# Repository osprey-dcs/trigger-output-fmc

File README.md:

# Trigger Output FMC

A single width HPC FMC board which provides 16 low jitter TTL outputs,
along with two Si5394 jitter cleaners with outputs connected to the MGTREF capable
when matched with the [LBL Marble](https://github.com/BerkeleyLab/Marble) FMC carrier.

This design is Open Hardware created by Osprey DCS and published under the terms of the
[CERN Open Hardware Licence Version 2 - Strongly Reciprocal](cern_ohl_s_v2.txt) license.

This repository contains KiCad 9.0.4 design files.

- [Data sheet](datasheet.md)
- [Current generated](https://osprey-dcs.github.io/trigger-output-fmc/)
  - [Schematic](https://osprey-dcs.github.io/trigger-output-fmc/trigger-output-fmc-schematic.pdf)
  - [BoM](https://osprey-dcs.github.io/trigger-output-fmc/trigger-output-fmc-bom.csv)
  - [STeP model](https://osprey-dcs.github.io/trigger-output-fmc/3D/trigger-output-fmc-3D.step)
  - [QA Procedure](https://osprey-dcs.github.io/trigger-output-fmc/QA.html)

## Block Diagram

## Status

Revision 1.0 produced and tested.

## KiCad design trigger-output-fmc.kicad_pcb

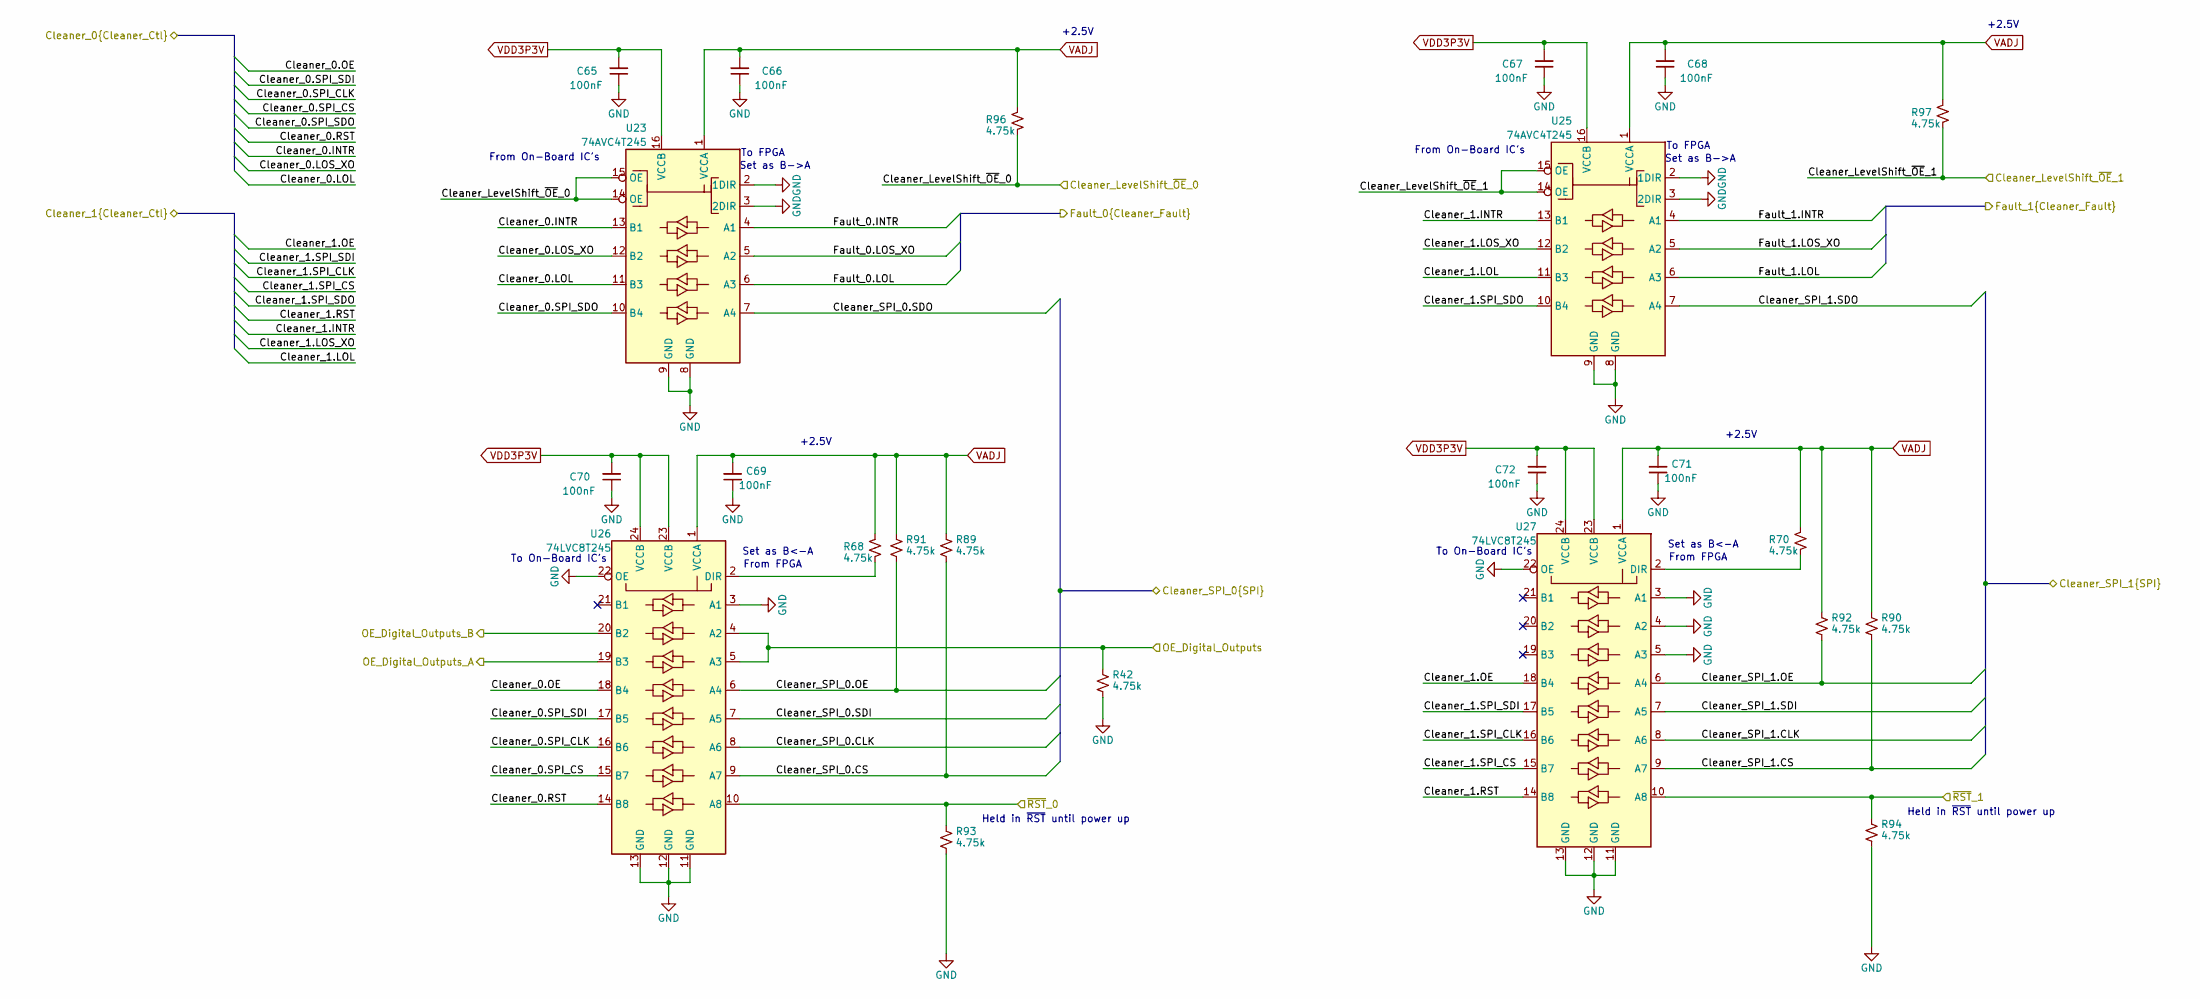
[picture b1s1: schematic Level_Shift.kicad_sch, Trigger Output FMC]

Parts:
C65, C66, C67, C68, C69, C70, C71, C72: 100nF; C_0402_1005Metric; MPN GCM155R71H104KE02J
R42, R68, R70, R89, R90, R91, R92, R93, R94, R96, R97: 4.75k; R_0402_1005Metric; MPN RC0402FR-074K75L
U23, U25: 74AVC4T245; TSSOP-16_4.4x5mm_P0.65mm; MPN SN74AVC4T245PWR
U26, U27: 74LVC8T245; TSSOP-24_4.4x7.8mm_P0.65mm; MPN SN74LVC8T245PWR

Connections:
/Digital IO/OE_A: U26.19 (B3); also elsewhere on the board
/Digital IO/OE_B: U26.20 (B2); also elsewhere on the board
/FMC/Cleaner_Fault_0.INTR: U23.4 (A1); also elsewhere on the board
/FMC/Cleaner_Fault_0.LOL: U23.6 (A3); also elsewhere on the board
/FMC/Cleaner_Fault_0.LOS_XO: U23.5 (A2); also elsewhere on the board
/FMC/Cleaner_Fault_1.INTR: U25.4 (A1); also elsewhere on the board
/FMC/Cleaner_Fault_1.LOL: U25.6 (A3); also elsewhere on the board
/FMC/Cleaner_Fault_1.LOS_XO: U25.5 (A2); also elsewhere on the board
/FMC/Cleaner_LevelShift_~OE_0: R96.1, U23.14 (OE), U23.15 (OE); also elsewhere on the board
/FMC/Cleaner_LevelShift_~OE_1: R97.1, U25.14 (OE), U25.15 (OE); also elsewhere on the board
/FMC/Cleaner_SPI_0.CLK: U26.8 (A6); also elsewhere on the board
/FMC/Cleaner_SPI_0.CS: R89.1, U26.9 (A7); also elsewhere on the board
/FMC/Cleaner_SPI_0.OE: R91.1, U26.6 (A4); also elsewhere on the board
/FMC/Cleaner_SPI_0.SDI: U26.7 (A5); also elsewhere on the board
/FMC/Cleaner_SPI_0.SDO: U23.7 (A4); also elsewhere on the board
/FMC/Cleaner_SPI_1.CLK: U27.8 (A6); also elsewhere on the board
/FMC/Cleaner_SPI_1.CS: R90.1, U27.9 (A7); also elsewhere on the board
/FMC/Cleaner_SPI_1.OE: R92.1, U27.6 (A4); also elsewhere on the board
/FMC/Cleaner_SPI_1.SDI: U27.7 (A5); also elsewhere on the board
/FMC/Cleaner_SPI_1.SDO: U25.7 (A4); also elsewhere on the board
/FMC/Cleaner_~RST_0: R93.2, U26.10 (A8); also elsewhere on the board
/FMC/Cleaner_~RST_1: R94.2, U27.10 (A8); also elsewhere on the board
/FMC/OE_Digital_Outputs: R42.2, U26.4 (A2), U26.5 (A3); also elsewhere on the board
/Jitter Cleaner0/Control.INTR: U23.13 (B1); also elsewhere on the board
/Jitter Cleaner0/Control.LOL: U23.11 (B3); also elsewhere on the board
/Jitter Cleaner0/Control.LOS_XO: U23.12 (B2); also elsewhere on the board
/Jitter Cleaner0/Control.OE: U26.18 (B4); also elsewhere on the board
/Jitter Cleaner0/Control.RST: U26.14 (B8); also elsewhere on the board
/Jitter Cleaner0/Control.SPI_CLK: U26.16 (B6); also elsewhere on the board
/Jitter Cleaner0/Control.SPI_CS: U26.15 (B7); also elsewhere on the board
/Jitter Cleaner0/Control.SPI_SDI: U26.17 (B5); also elsewhere on the board
/Jitter Cleaner0/Control.SPI_SDO: U23.10 (B4); also elsewhere on the board
/Jitter Cleaner1/Control.INTR: U25.13 (B1); also elsewhere on the board
/Jitter Cleaner1/Control.LOL: U25.11 (B3); also elsewhere on the board
/Jitter Cleaner1/Control.LOS_XO: U25.12 (B2); also elsewhere on the board
/Jitter Cleaner1/Control.OE: U27.18 (B4); also elsewhere on the board
/Jitter Cleaner1/Control.RST: U27.14 (B8); also elsewhere on the board
/Jitter Cleaner1/Control.SPI_CLK: U27.16 (B6); also elsewhere on the board
/Jitter Cleaner1/Control.SPI_CS: U27.15 (B7); also elsewhere on the board
/Jitter Cleaner1/Control.SPI_SDI: U27.17 (B5); also elsewhere on the board
/Jitter Cleaner1/Control.SPI_SDO: U25.10 (B4); also elsewhere on the board
GND: C65.1, C66.1, C67.1, C68.1, C69.1, C70.1, C71.1, C72.1, R42.1, R93.1, R94.1, U23.2 (1DIR), U23.3 (2DIR), U23.8 (GND), U23.9 (GND), U25.2 (1DIR), U25.3 (2DIR), U25.8 (GND), U25.9 (GND), U26.3 (A1), U26.11 (GND), U26.12 (GND), U26.13 (GND), U26.22 (OE), U27.3 (A1), U27.4 (A2), U27.5 (A3), U27.11 (GND), U27.12 (GND), U27.13 (GND), U27.22 (OE); also elsewhere on the board
unnamed: R68.1, U26.2 (DIR)
unnamed: R70.1, U27.2 (DIR)
VADJ: C66.2, C68.2, C69.2, C71.2, R68.2, R70.2, R89.2, R90.2, R91.2, R92.2, R96.2, R97.2, U23.1 (VCCA), U25.1 (VCCA), U26.1 (VCCA), U27.1 (VCCA); also elsewhere on the board
VDD3P3V: C65.2, C67.2, C70.2, C72.2, U23.16 (VCCB), U25.16 (VCCB), U26.23 (VCCB), U26.24 (VCCB), U27.23 (VCCB), U27.24 (VCCB); also elsewhere on the board

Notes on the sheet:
Held in ~{RST} until power up
To FPGA
To On-Board IC's
+2.5V
From On-Board IC's
Set as B<-A
From FPGA
Set as B->A
Set as B<-A

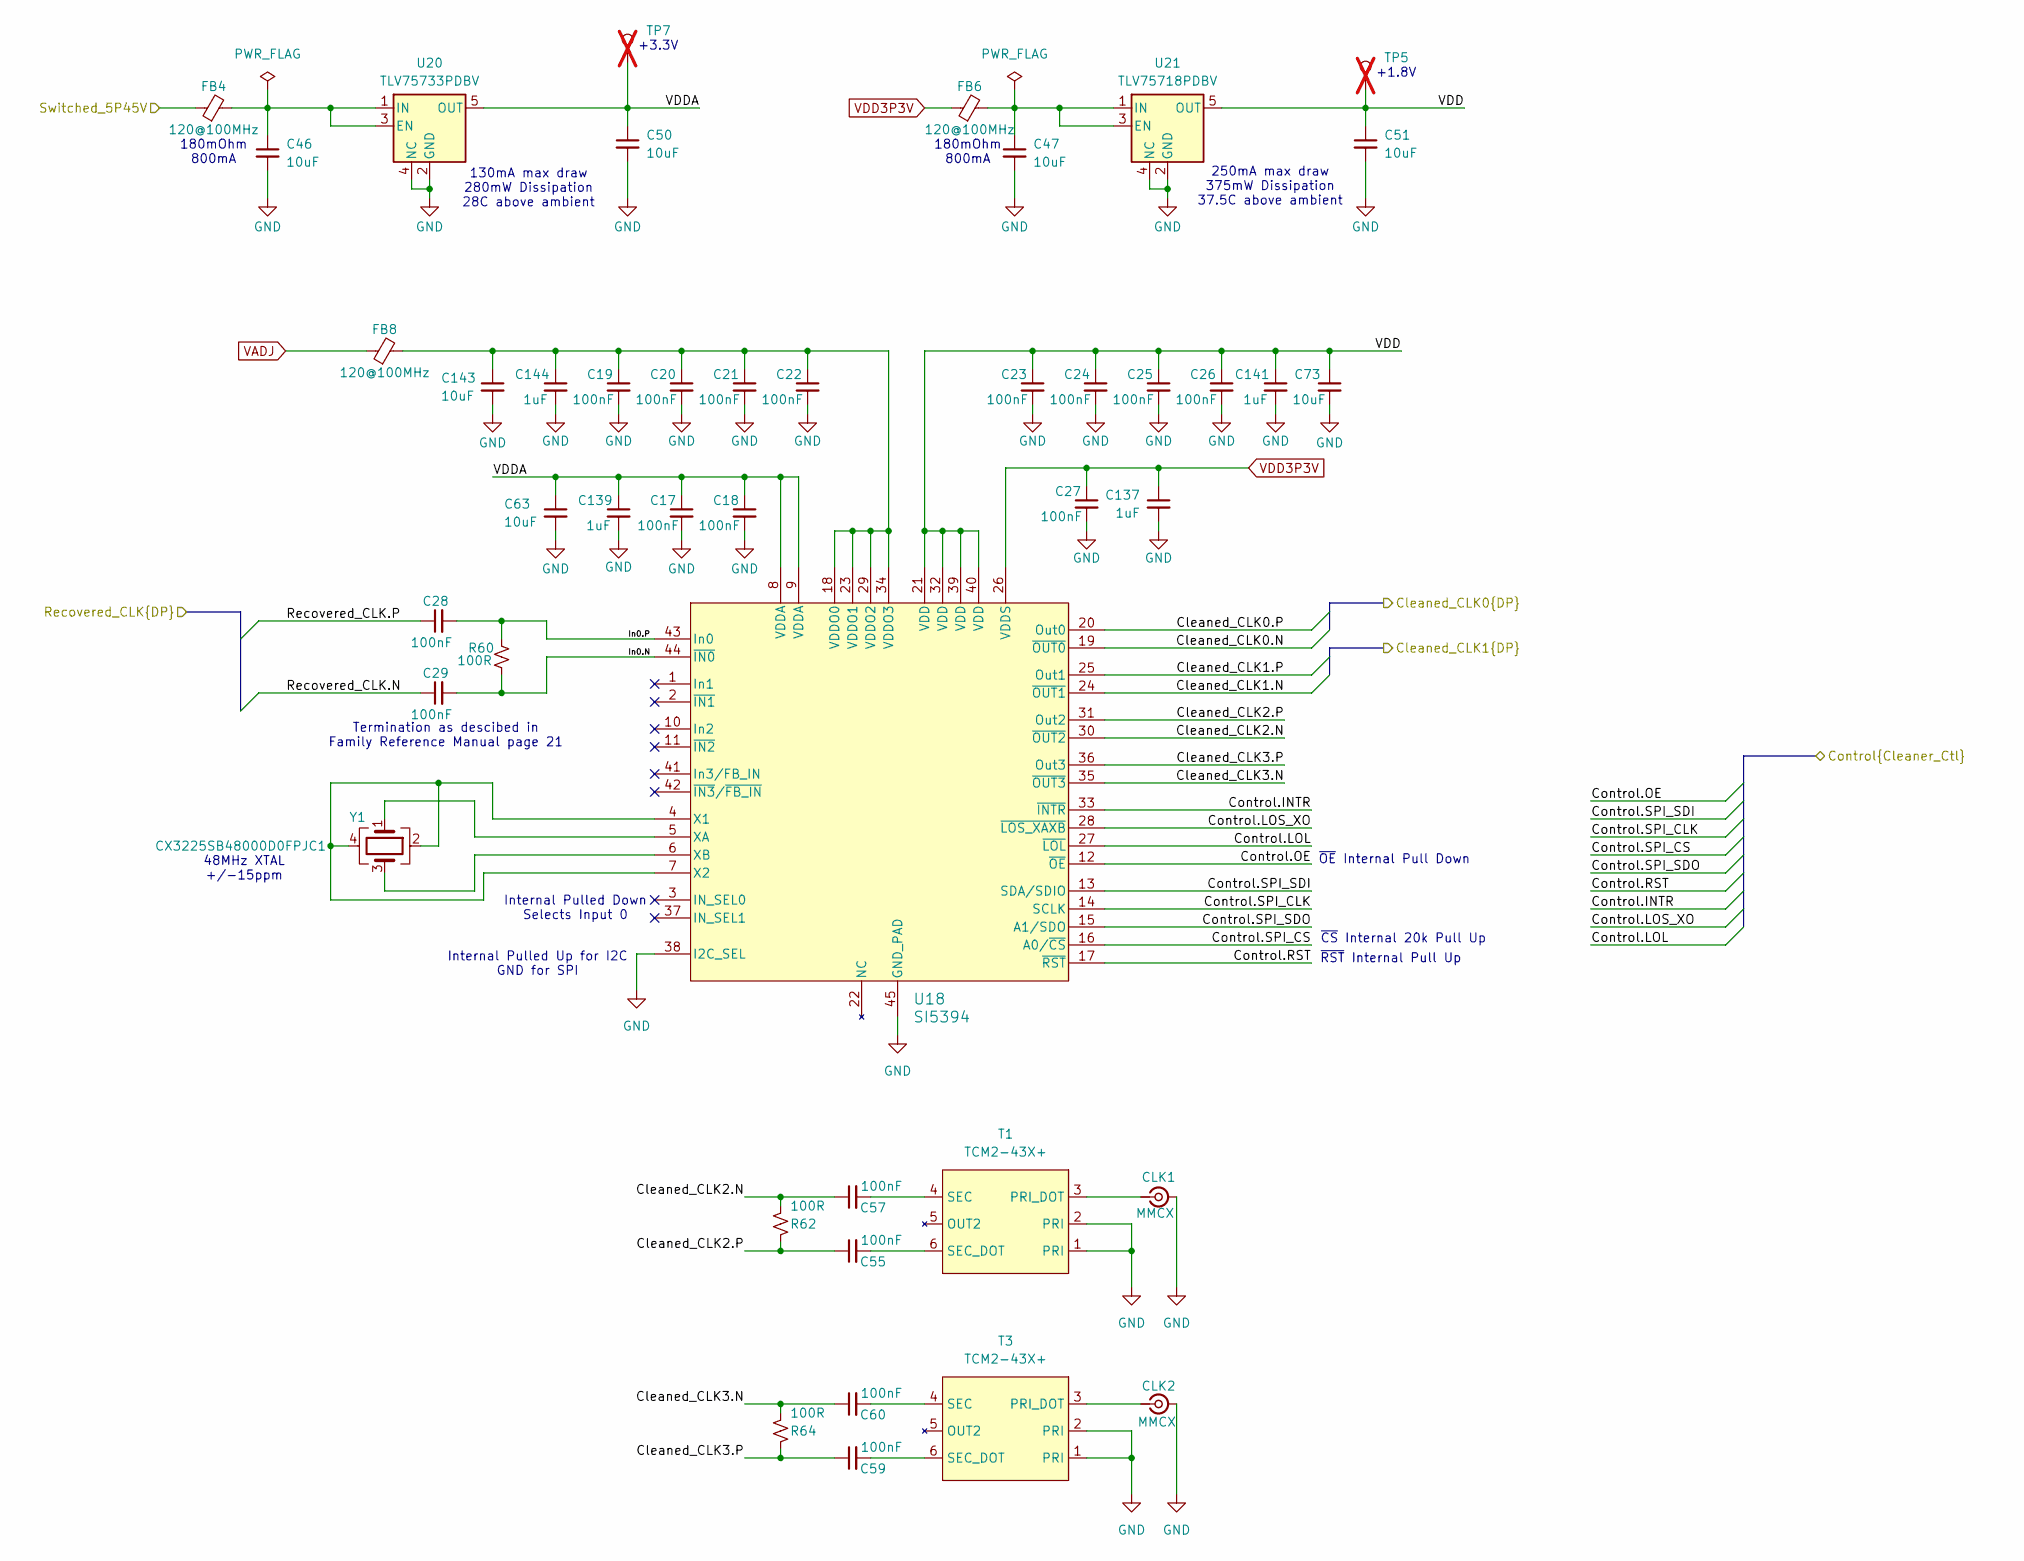
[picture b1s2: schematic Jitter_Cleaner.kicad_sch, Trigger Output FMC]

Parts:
C17, C18, C19, C20, C21, C22, C23, C24, C25, C26, C27, C28, C29, C55, C57, C59, C60: 100nF; C_0402_1005Metric; MPN GCM155R71H104KE02J
C46, C47, C50, C51, C63, C73, C143: 10uF; C_0805_2012Metric; MPN TMK212BBJ106MG-T
C137, C139, C141, C144: 1uF; C_0603_1608Metric; MPN GCM188R71E105KA64D
CLK1, CLK2: MMCX; MMCX_Molex_73415-1471_Vertical; MPN MMCX-J-P-H-ST-TH1
FB4, FB6, FB8: 120@100MHz; L_0603_1608Metric; MPN BLM18AG121SN1D
R60: 100R; R_0402_1005Metric; MPN RC0402FR-07100RL
R62, R64: 100R; R_0603_1608Metric; MPN RG1608P-101-B-T5
T1, T3: TCM2-43X+; Mini-Circuits_DB1627_rounded_pads; MPN TCM2-43X+
TP5, TP7: Keystone5000; TestPoint_Keystone_5000-5004_Miniature; MPN 5000; not fitted
U18: SI5394; QFN-44-1EP_7x7mm_P0.5mm_EP5.2x5.2mm_ThermalVias; MPN SI5394A-A-GM
U20: TLV75733PDBV; SOT-23-5; MPN TLV75733PDBV
U21: TLV75718PDBV; SOT-23-5; MPN TLV75718PDBV
Y1: CX3225SB48000D0FPJC1; Crystal_SMD_Abracon_ABM8AIG-4Pin_3.2x2.5mm; MPN CX3225SB48000D0FPJC1

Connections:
/Digital IO/Switched_5P45V: FB4.1; also elsewhere on the board
/FMC/Cleaned_CLK_0.N: U18.19 (~OUT0); also elsewhere on the board
/FMC/Cleaned_CLK_0.P: U18.20 (Out0); also elsewhere on the board
/FMC/FMC_GBTCLK0.N: U18.24 (~OUT1); also elsewhere on the board
/FMC/FMC_GBTCLK0.P: U18.25 (Out1); also elsewhere on the board
/FMC/Recovered_CLK_0.N: C29.1; also elsewhere on the board
/FMC/Recovered_CLK_0.P: C28.1; also elsewhere on the board
/Jitter Cleaner0/Cleaned_CLK2.N: C57.1, R62.2, U18.30 (~OUT2)
/Jitter Cleaner0/Cleaned_CLK2.P: C55.1, R62.1, U18.31 (Out2)
/Jitter Cleaner0/Cleaned_CLK3.N: C60.1, R64.2, U18.35 (~OUT3)
/Jitter Cleaner0/Cleaned_CLK3.P: C59.1, R64.1, U18.36 (Out3)
/Jitter Cleaner0/Control.INTR: U18.33 (~INTR); also elsewhere on the board
/Jitter Cleaner0/Control.LOL: U18.27 (~LOL); also elsewhere on the board
/Jitter Cleaner0/Control.LOS_XO: U18.28 (~LOS_XAXB); also elsewhere on the board
/Jitter Cleaner0/Control.OE: U18.12 (~OE); also elsewhere on the board
/Jitter Cleaner0/Control.RST: U18.17 (~RST); also elsewhere on the board
/Jitter Cleaner0/Control.SPI_CLK: U18.14 (SCLK); also elsewhere on the board
/Jitter Cleaner0/Control.SPI_CS: U18.16 (A0/~CS); also elsewhere on the board
/Jitter Cleaner0/Control.SPI_SDI: U18.13 (SDA/SDIO); also elsewhere on the board
/Jitter Cleaner0/Control.SPI_SDO: U18.15 (A1/SDO); also elsewhere on the board
/Jitter Cleaner0/In0.N: C29.2, R60.2, U18.44 (~IN0)
/Jitter Cleaner0/In0.P: C28.2, R60.1, U18.43 (In0)
/Jitter Cleaner0/VDD: C23.1, C24.1, C25.1, C26.1, C51.1, C73.1, C141.1, TP5.1, U18.21 (VDD), U18.32 (VDD), U18.39 (VDD), U18.40 (VDD), U21.5 (OUT)
/Jitter Cleaner0/VDDA: C17.1, C18.1, C50.1, C63.1, C139.1, TP7.1, U18.8 (VDDA), U18.9 (VDDA), U20.5 (OUT)
GND: C17.2, C18.2, C19.2, C20.2, C21.2, C22.2, C23.2, C24.2, C25.2, C26.2, C27.2, C46.2, C47.2, C50.2, C51.2, C63.2, C73.2, C137.2, C139.2, C141.2, C143.2, C144.2, CLK1.2 (Ext), CLK2.2 (Ext), T1.1 (PRI), T1.2 (PRI), T3.1 (PRI), T3.2 (PRI), U18.38 (I2C_SEL), U18.45 (GND_PAD), U20.2 (GND), U20.4 (NC), U21.2 (GND), U21.4 (NC); also elsewhere on the board
unnamed: CLK1.1 (In), T1.3 (PRI_DOT)
unnamed: CLK2.1 (In), T3.3 (PRI_DOT)
unnamed: C57.2, T1.4 (SEC)
unnamed: C55.2, T1.6 (SEC_DOT)
unnamed: C60.2, T3.4 (SEC)
unnamed: C59.2, T3.6 (SEC_DOT)
unnamed: C19.1, C20.1, C21.1, C22.1, C143.1, C144.1, FB8.2, U18.18 (VDDO0), U18.23 (VDDO1), U18.29 (VDDO2), U18.34 (VDDO3)
unnamed: U18.4 (X1), U18.7 (X2), Y1.2, Y1.4
unnamed: U18.5 (XA), Y1.1
unnamed: U18.6 (XB), Y1.3
unnamed: C46.1, FB4.2, U20.1 (IN), U20.3 (EN)
unnamed: C47.1, FB6.2, U21.1 (IN), U21.3 (EN)
VADJ: FB8.1; also elsewhere on the board
VDD3P3V: C27.1, C137.1, FB6.1, U18.26 (VDDS); also elsewhere on the board

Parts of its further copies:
C30, C31, C32, C36, C37, C38, C39, C40, C41, C42, C43, C44, C45, C56, C58, C61, C62: 100nF; C_0402_1005Metric; MPN GCM155R71H104KE02J
C64, C74, C75, C76, C77, C78, C145: 10uF; C_0805_2012Metric; MPN TMK212BBJ106MG-T
C138, C140, C142, C146: 1uF; C_0603_1608Metric; MPN GCM188R71E105KA64D
CLK3, CLK4: MMCX; MMCX_Molex_73415-1471_Vertical; MPN MMCX-J-P-H-ST-TH1
FB5, FB7, FB9: 120@100MHz; L_0603_1608Metric; MPN BLM18AG121SN1D
R61: 100R; R_0402_1005Metric; MPN RC0402FR-07100RL
R63, R65: 100R; R_0603_1608Metric; MPN RG1608P-101-B-T5
T2, T4: TCM2-43X+; Mini-Circuits_DB1627_rounded_pads; MPN TCM2-43X+
TP6, TP9: Keystone5000; TestPoint_Keystone_5000-5004_Miniature; MPN 5000; not fitted
U19: SI5394; QFN-44-1EP_7x7mm_P0.5mm_EP5.2x5.2mm_ThermalVias; MPN SI5394A-A-GM
U24: TLV75733PDBV; SOT-23-5; MPN TLV75733PDBV
U28: TLV75718PDBV; SOT-23-5; MPN TLV75718PDBV
Y2: CX3225SB48000D0FPJC1; Crystal_SMD_Abracon_ABM8AIG-4Pin_3.2x2.5mm; MPN CX3225SB48000D0FPJC1

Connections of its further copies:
/Digital IO/Switched_5P45V: FB5.1; also elsewhere on the board
/FMC/Cleaned_CLK_1.N: U19.24 (~OUT1); also elsewhere on the board
/FMC/Cleaned_CLK_1.P: U19.25 (Out1); also elsewhere on the board
/FMC/FMC_GBTCLK1.N: U19.19 (~OUT0); also elsewhere on the board
/FMC/FMC_GBTCLK1.P: U19.20 (Out0); also elsewhere on the board
/FMC/Recovered_CLK_1.N: C31.1; also elsewhere on the board
/FMC/Recovered_CLK_1.P: C30.1; also elsewhere on the board
/Jitter Cleaner1/Cleaned_CLK2.N: C58.1, R63.2, U19.30 (~OUT2)
/Jitter Cleaner1/Cleaned_CLK2.P: C56.1, R63.1, U19.31 (Out2)
/Jitter Cleaner1/Cleaned_CLK3.N: C62.1, R65.2, U19.35 (~OUT3)
/Jitter Cleaner1/Cleaned_CLK3.P: C61.1, R65.1, U19.36 (Out3)
/Jitter Cleaner1/Control.INTR: U19.33 (~INTR); also elsewhere on the board
/Jitter Cleaner1/Control.LOL: U19.27 (~LOL); also elsewhere on the board
/Jitter Cleaner1/Control.LOS_XO: U19.28 (~LOS_XAXB); also elsewhere on the board
/Jitter Cleaner1/Control.OE: U19.12 (~OE); also elsewhere on the board
/Jitter Cleaner1/Control.RST: U19.17 (~RST); also elsewhere on the board
/Jitter Cleaner1/Control.SPI_CLK: U19.14 (SCLK); also elsewhere on the board
/Jitter Cleaner1/Control.SPI_CS: U19.16 (A0/~CS); also elsewhere on the board
/Jitter Cleaner1/Control.SPI_SDI: U19.13 (SDA/SDIO); also elsewhere on the board
/Jitter Cleaner1/Control.SPI_SDO: U19.15 (A1/SDO); also elsewhere on the board
/Jitter Cleaner1/In0.N: C31.2, R61.2, U19.44 (~IN0)
/Jitter Cleaner1/In0.P: C30.2, R61.1, U19.43 (In0)
/Jitter Cleaner1/VDD: C41.1, C43.1, C44.1, C45.1, C74.1, C78.1, C142.1, TP9.1, U19.21 (VDD), U19.32 (VDD), U19.39 (VDD), U19.40 (VDD), U28.5 (OUT)
/Jitter Cleaner1/VDDA: C37.1, C39.1, C64.1, C76.1, C140.1, TP6.1, U19.8 (VDDA), U19.9 (VDDA), U24.5 (OUT)
GND: C32.2, C36.2, C37.2, C38.2, C39.2, C40.2, C41.2, C42.2, C43.2, C44.2, C45.2, C64.2, C74.2, C75.2, C76.2, C77.2, C78.2, C138.2, C140.2, C142.2, C145.2, C146.2, CLK3.2 (Ext), CLK4.2 (Ext), T2.1 (PRI), T2.2 (PRI), T4.1 (PRI), T4.2 (PRI), U19.38 (I2C_SEL), U19.45 (GND_PAD), U24.2 (GND), U24.4 (NC), U28.2 (GND), U28.4 (NC); also elsewhere on the board
unnamed: CLK3.1 (In), T2.3 (PRI_DOT)
unnamed: CLK4.1 (In), T4.3 (PRI_DOT)
unnamed: C58.2, T2.4 (SEC)
unnamed: C56.2, T2.6 (SEC_DOT)
unnamed: C62.2, T4.4 (SEC)
unnamed: C61.2, T4.6 (SEC_DOT)
unnamed: C32.1, C36.1, C38.1, C40.1, C145.1, C146.1, FB9.2, U19.18 (VDDO0), U19.23 (VDDO1), U19.29 (VDDO2), U19.34 (VDDO3)
unnamed: U19.4 (X1), U19.7 (X2), Y2.2, Y2.4
unnamed: U19.5 (XA), Y2.1
unnamed: U19.6 (XB), Y2.3
unnamed: C75.1, FB5.2, U24.1 (IN), U24.3 (EN)
unnamed: C77.1, FB7.2, U28.1 (IN), U28.3 (EN)
VADJ: FB9.1; also elsewhere on the board
VDD3P3V: C42.1, C138.1, FB7.1, U19.26 (VDDS); also elsewhere on the board

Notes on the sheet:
130mA max draw 280mW Dissipation 28C above ambient
~{CS} Internal 20k Pull Up
Internal Pulled Up for I2C GND for SPI
48MHz XTAL +/-15ppm
180mOhm 800mA
250mA max draw 375mW Dissipation 37.5C above ambient
~{RST} Internal Pull Up
Termination as descibed in Family Reference Manual page 21
+1.8V
+3.3V
Internal Pulled Down Selects Input 0
~{OE} Internal Pull Down

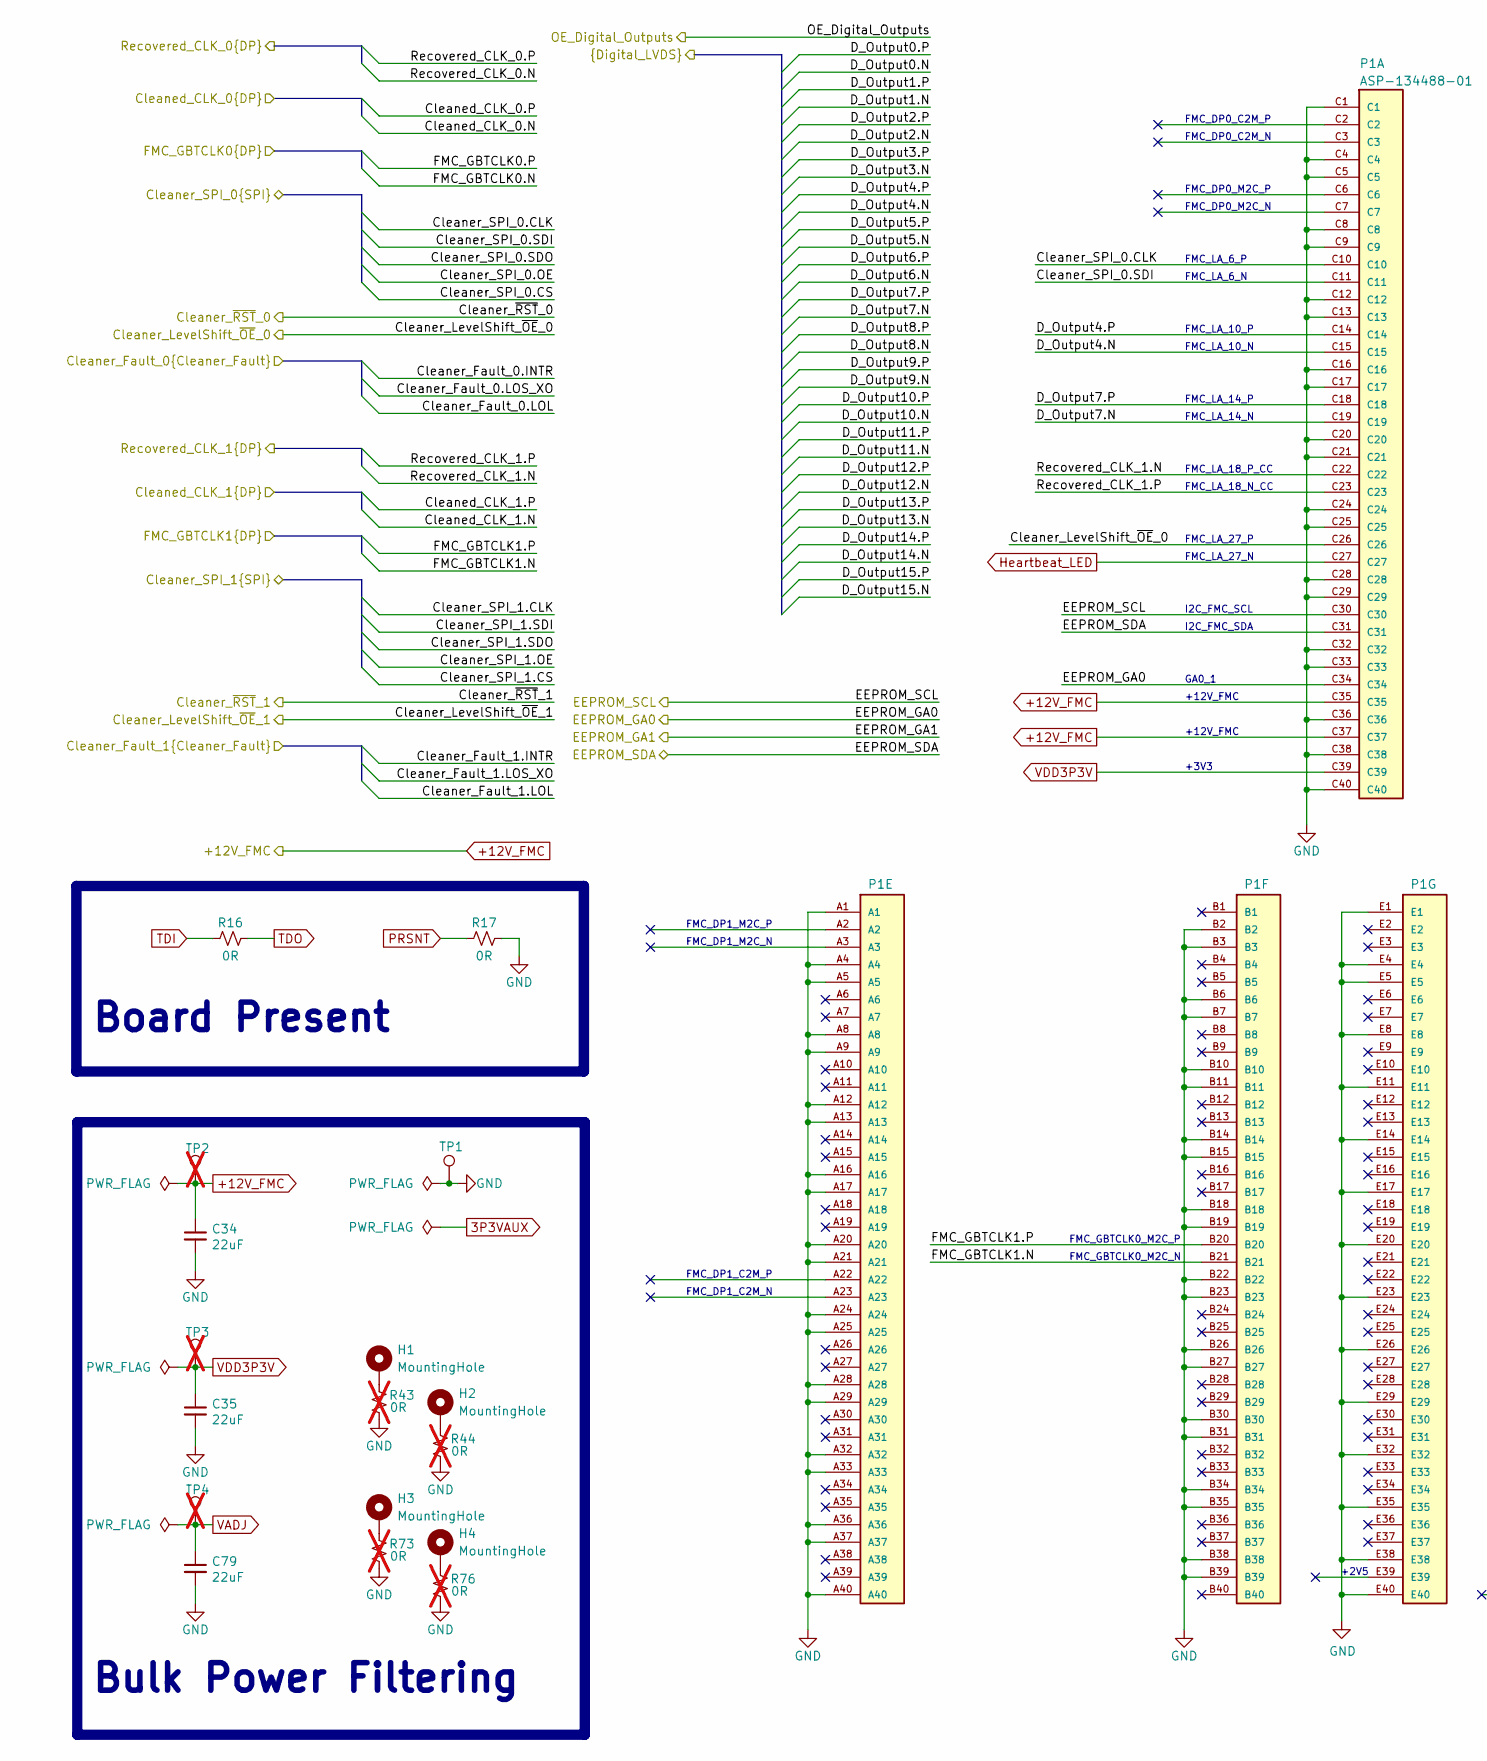
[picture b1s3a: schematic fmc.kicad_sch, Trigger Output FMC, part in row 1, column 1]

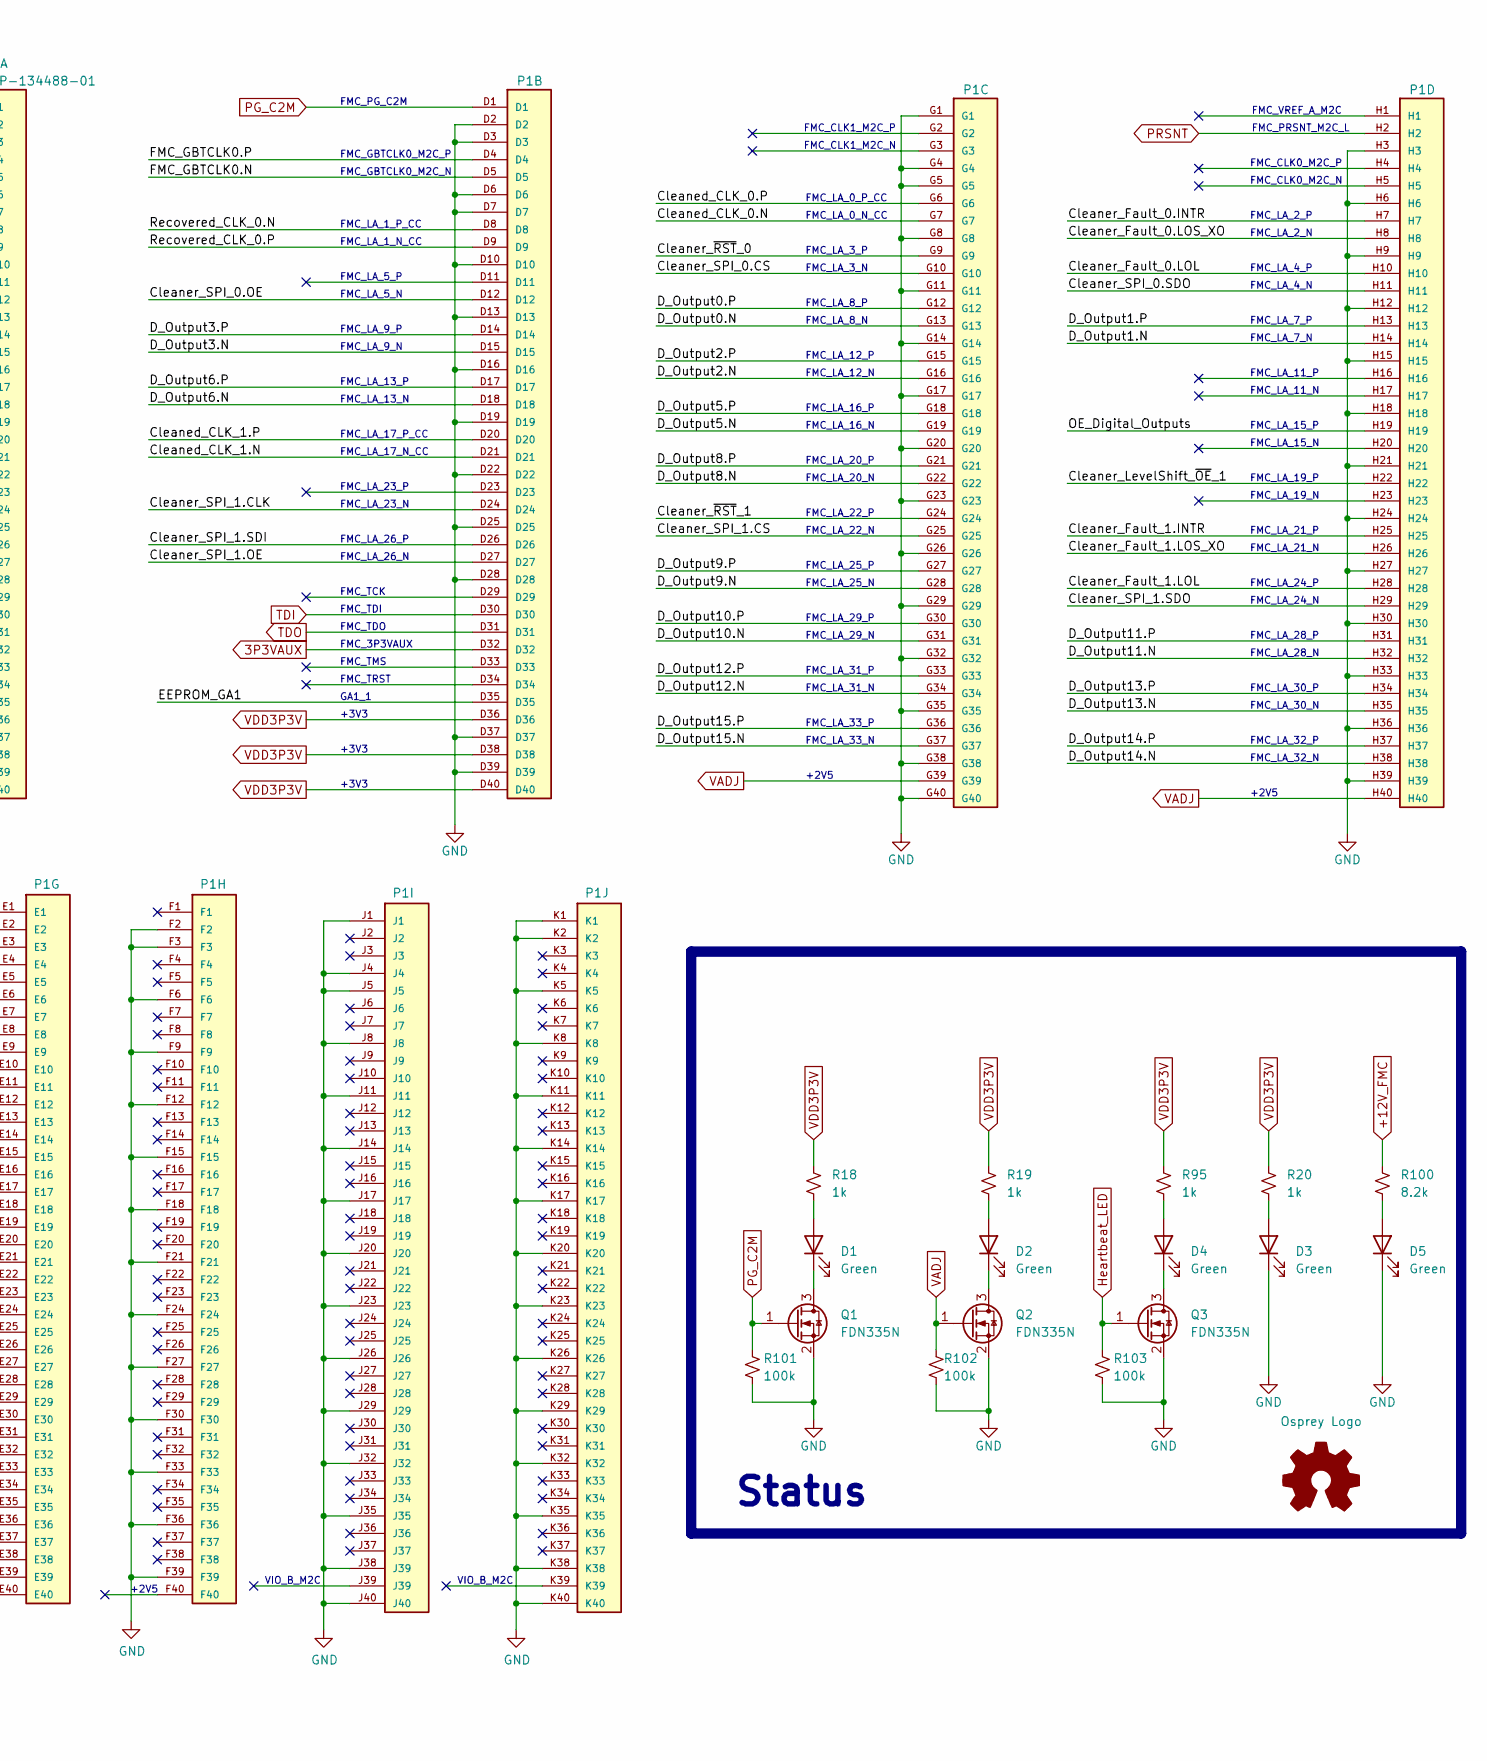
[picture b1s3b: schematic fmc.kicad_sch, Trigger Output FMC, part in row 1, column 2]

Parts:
C34, C35, C79: 22uF; C_1210_3225Metric; MPN GMK325BJ226MM-P
D1, D2, D3, D4, D5: Green; LED_0603_1608Metric; MPN APT1608CGCK
H1, H2: MountingHole; MountingHole_3.0mm_M2.5_Pad_3.3mm_UniversalMarbleSlot
H3, H4: MountingHole; MountingHole_3.0mm_3.8mm_Pad_3.3mm_UniversalMarbleSlot
Logo1: Osprey Logo; Logo_2X
P1: ASP-134488-01; Samtec_FMC_ASP-134602-01_10x40_P1.27mm_Vertical; MPN ASP-134488-01
Q1, Q2, Q3: FDN335N; SOT-23; MPN FDN335N
R16, R17: 0R; R_0603_1608Metric; MPN ERJ-3GEY0R00V
R18, R19, R20, R95: 1k; R_0603_1608Metric; MPN ESR03EZPF1001
R43, R44, R73, R76: 0R; R_0805_2012Metric; not fitted
R100: 8.2k; R_0603_1608Metric; MPN RC0603FR-078K2L
R101, R102, R103: 100k; R_0603_1608Metric; MPN RC0603FR-07100KL
TP1: Keystone5001; TestPoint_Keystone_5000-5004_Miniature; MPN 5001
TP2, TP3, TP4: Keystone5000; TestPoint_Keystone_5000-5004_Miniature; MPN 5000; not fitted

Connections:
3P3VAUX: P1.D32; also elsewhere on the board
+12V_FMC: C34.1, P1.C35, P1.C37, R100.2, TP2.1; also elsewhere on the board
/Digital IO/D_Output0.N: P1.G13; also elsewhere on the board
/Digital IO/D_Output0.P: P1.G12; also elsewhere on the board
/Digital IO/D_Output1.N: P1.H14; also elsewhere on the board
/Digital IO/D_Output1.P: P1.H13; also elsewhere on the board
/Digital IO/D_Output2.N: P1.G16; also elsewhere on the board
/Digital IO/D_Output2.P: P1.G15; also elsewhere on the board
/Digital IO/D_Output3.N: P1.D15; also elsewhere on the board
/Digital IO/D_Output3.P: P1.D14; also elsewhere on the board
/Digital IO/D_Output4.N: P1.C15; also elsewhere on the board
/Digital IO/D_Output4.P: P1.C14; also elsewhere on the board
/Digital IO/D_Output5.N: P1.G19; also elsewhere on the board
/Digital IO/D_Output5.P: P1.G18; also elsewhere on the board
/Digital IO/D_Output6.N: P1.D18; also elsewhere on the board
/Digital IO/D_Output6.P: P1.D17; also elsewhere on the board
/Digital IO/D_Output7.N: P1.C19; also elsewhere on the board
/Digital IO/D_Output7.P: P1.C18; also elsewhere on the board
/Digital IO/D_Output8.N: P1.G22; also elsewhere on the board
/Digital IO/D_Output8.P: P1.G21; also elsewhere on the board
/Digital IO/D_Output9.N: P1.G28; also elsewhere on the board
/Digital IO/D_Output9.P: P1.G27; also elsewhere on the board
/Digital IO/D_Output10.N: P1.G31; also elsewhere on the board
/Digital IO/D_Output10.P: P1.G30; also elsewhere on the board
/Digital IO/D_Output11.N: P1.H32; also elsewhere on the board
/Digital IO/D_Output11.P: P1.H31; also elsewhere on the board
/Digital IO/D_Output12.N: P1.G34; also elsewhere on the board
/Digital IO/D_Output12.P: P1.G33; also elsewhere on the board
/Digital IO/D_Output13.N: P1.H35; also elsewhere on the board
/Digital IO/D_Output13.P: P1.H34; also elsewhere on the board
/Digital IO/D_Output14.N: P1.H38; also elsewhere on the board
/Digital IO/D_Output14.P: P1.H37; also elsewhere on the board
/Digital IO/D_Output15.N: P1.G37; also elsewhere on the board
/Digital IO/D_Output15.P: P1.G36; also elsewhere on the board
/FMC/Cleaned_CLK_0.N: P1.G7; also elsewhere on the board
/FMC/Cleaned_CLK_0.P: P1.G6; also elsewhere on the board
/FMC/Cleaned_CLK_1.N: P1.D21; also elsewhere on the board
/FMC/Cleaned_CLK_1.P: P1.D20; also elsewhere on the board
/FMC/Cleaner_Fault_0.INTR: P1.H7; also elsewhere on the board
/FMC/Cleaner_Fault_0.LOL: P1.H10; also elsewhere on the board
/FMC/Cleaner_Fault_0.LOS_XO: P1.H8; also elsewhere on the board
/FMC/Cleaner_Fault_1.INTR: P1.H25; also elsewhere on the board
/FMC/Cleaner_Fault_1.LOL: P1.H28; also elsewhere on the board
/FMC/Cleaner_Fault_1.LOS_XO: P1.H26; also elsewhere on the board
/FMC/Cleaner_LevelShift_~OE_0: P1.C26; also elsewhere on the board
/FMC/Cleaner_LevelShift_~OE_1: P1.H22; also elsewhere on the board
/FMC/Cleaner_SPI_0.CLK: P1.C10; also elsewhere on the board
/FMC/Cleaner_SPI_0.CS: P1.G10; also elsewhere on the board
/FMC/Cleaner_SPI_0.OE: P1.D12; also elsewhere on the board
/FMC/Cleaner_SPI_0.SDI: P1.C11; also elsewhere on the board
/FMC/Cleaner_SPI_0.SDO: P1.H11; also elsewhere on the board
/FMC/Cleaner_SPI_1.CLK: P1.D24; also elsewhere on the board
/FMC/Cleaner_SPI_1.CS: P1.G25; also elsewhere on the board
/FMC/Cleaner_SPI_1.OE: P1.D27; also elsewhere on the board
/FMC/Cleaner_SPI_1.SDI: P1.D26; also elsewhere on the board
/FMC/Cleaner_SPI_1.SDO: P1.H29; also elsewhere on the board
/FMC/Cleaner_~RST_0: P1.G9; also elsewhere on the board
/FMC/Cleaner_~RST_1: P1.G24; also elsewhere on the board
/FMC/EEPROM_GA0: P1.C34; also elsewhere on the board
/FMC/EEPROM_GA1: P1.D35; also elsewhere on the board
/FMC/EEPROM_SCL: P1.C30; also elsewhere on the board
/FMC/EEPROM_SDA: P1.C31; also elsewhere on the board
/FMC/FMC_GBTCLK0.N: P1.D5; also elsewhere on the board
/FMC/FMC_GBTCLK0.P: P1.D4; also elsewhere on the board
/FMC/FMC_GBTCLK1.N: P1.B21; also elsewhere on the board
/FMC/FMC_GBTCLK1.P: P1.B20; also elsewhere on the board
/FMC/OE_Digital_Outputs: P1.H19; also elsewhere on the board
/FMC/Recovered_CLK_0.N: P1.D8; also elsewhere on the board
/FMC/Recovered_CLK_0.P: P1.D9; also elsewhere on the board
/FMC/Recovered_CLK_1.N: P1.C22; also elsewhere on the board
/FMC/Recovered_CLK_1.P: P1.C23; also elsewhere on the board
GND: C34.2, C35.2, C79.2, D3.1 (K), D5.1 (K), P1.A1, P1.A4, P1.A5, P1.A8, P1.A9, P1.A12, P1.A13, P1.A16, P1.A17, P1.A20, P1.A21, P1.A24, P1.A25, P1.A28, P1.A29, P1.A32, P1.A33, P1.A36, P1.A37, P1.A40, P1.B2, P1.B3, P1.B6, P1.B7, P1.B10, P1.B11, P1.B14, P1.B15, P1.B18, P1.B19, P1.B22, P1.B23, P1.B26, P1.B27, P1.B30, P1.B31, P1.B34, P1.B35, P1.B38, P1.B39, P1.C1, P1.C4, P1.C5, P1.C8, P1.C9, P1.C12, P1.C13, P1.C16, P1.C17, P1.C20, P1.C21, P1.C24, P1.C25, P1.C28, P1.C29, P1.C32, P1.C33, P1.C36, P1.C38, P1.C40, P1.D2, P1.D3, P1.D6, P1.D7, P1.D10, P1.D13, P1.D16, P1.D19, P1.D22, P1.D25, P1.D28, P1.D37, P1.D39, P1.E1, P1.E4, P1.E5, P1.E8, P1.E11, P1.E14, P1.E17, P1.E20, P1.E23, P1.E26, P1.E29, P1.E32, P1.E35, P1.E38, P1.E40, P1.F2, P1.F3, P1.F6, P1.F9, P1.F12, P1.F15, P1.F18, P1.F21, P1.F24, P1.F27, P1.F30, P1.F33, P1.F36, P1.F39, P1.G1, P1.G4, P1.G5, P1.G8, P1.G11, P1.G14, P1.G17, P1.G20, P1.G23, P1.G26, P1.G29, P1.G32, P1.G35, P1.G38, P1.G40, P1.H3, P1.H6, P1.H9, P1.H12, P1.H15, P1.H18, P1.H21, P1.H24, P1.H27, P1.H30, P1.H33, P1.H36, P1.H39, P1.J1, P1.J4, P1.J5, P1.J8, P1.J11, P1.J14, P1.J17, P1.J20, P1.J23, P1.J26, P1.J29, P1.J32, P1.J35, P1.J38 (J39), P1.J40, P1.K1, P1.K2, P1.K5, P1.K8, P1.K11, P1.K14, P1.K17, P1.K20, P1.K23, P1.K26, P1.K29, P1.K32, P1.K35, P1.K38, P1.K40, Q1.2 (S), Q2.2 (S), Q3.2 (S), R17.2, R43.1, R44.1, R73.1, R76.1, R101.1, R102.1, R103.1, TP1.1; also elsewhere on the board
Heartbeat_LED: P1.C27, Q3.1 (G), R103.2
unnamed: D1.2 (A), R18.1
unnamed: D1.1 (K), Q1.3 (D)
unnamed: D2.2 (A), R19.1
unnamed: D2.1 (K), Q2.3 (D)
unnamed: D3.2 (A), R20.1
unnamed: D4.2 (A), R95.1
unnamed: D4.1 (K), Q3.3 (D)
unnamed: D5.2 (A), R100.1
unnamed: H1.1, R43.2
unnamed: H2.1, R44.2
unnamed: H3.1, R73.2
unnamed: H4.1, R76.2
PG_C2M: P1.D1, Q1.1 (G), R101.2
PRSNT: P1.H2, R17.1
TDI: P1.D30, R16.2
TDO: P1.D31, R16.1
VADJ: C79.1, P1.G39, P1.H40, Q2.1 (G), R102.2, TP4.1; also elsewhere on the board
VDD3P3V: C35.1, P1.C39, P1.D36, P1.D38, P1.D40, R18.2, R19.2, R20.2, R95.2, TP3.1; also elsewhere on the board

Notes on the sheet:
FMC_LA_19_N
FMC_GBTCLK0_M2C_N
FMC_LA_3_P
FMC_LA_5_P
FMC_LA_32_P
FMC_CLK0_M2C_P
VIO_B_M2C
FMC_LA_4_P
FMC_LA_26_N
FMC_LA_20_P
FMC_LA_21_N
FMC_LA_29_N
FMC_LA_14_N
Board Present
FMC_LA_21_P
FMC_LA_22_P
FMC_LA_18_N_CC
FMC_3P3VAUX
FMC_LA_6_P
FMC_LA_19_P
FMC_LA_7_N
FMC_LA_30_P
Status
+2V5
FMC_VREF_A_M2C
FMC_CLK0_M2C_N
FMC_LA_9_N
FMC_LA_2_N
FMC_LA_16_P
FMC_LA_31_P
FMC_LA_10_N
+3V3
FMC_LA_14_P
FMC_LA_32_N
GA0_1
FMC_LA_1_P_CC
FMC_DP1_M2C_P
FMC_TDI
+3V3
FMC_LA_11_P

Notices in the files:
Digital_IO.kicad_sch:
SPDX-FileCopyrightText: 2025 Osprey DCS
SPDX-License-Identifier: CERN-OHL-S-2.0+
